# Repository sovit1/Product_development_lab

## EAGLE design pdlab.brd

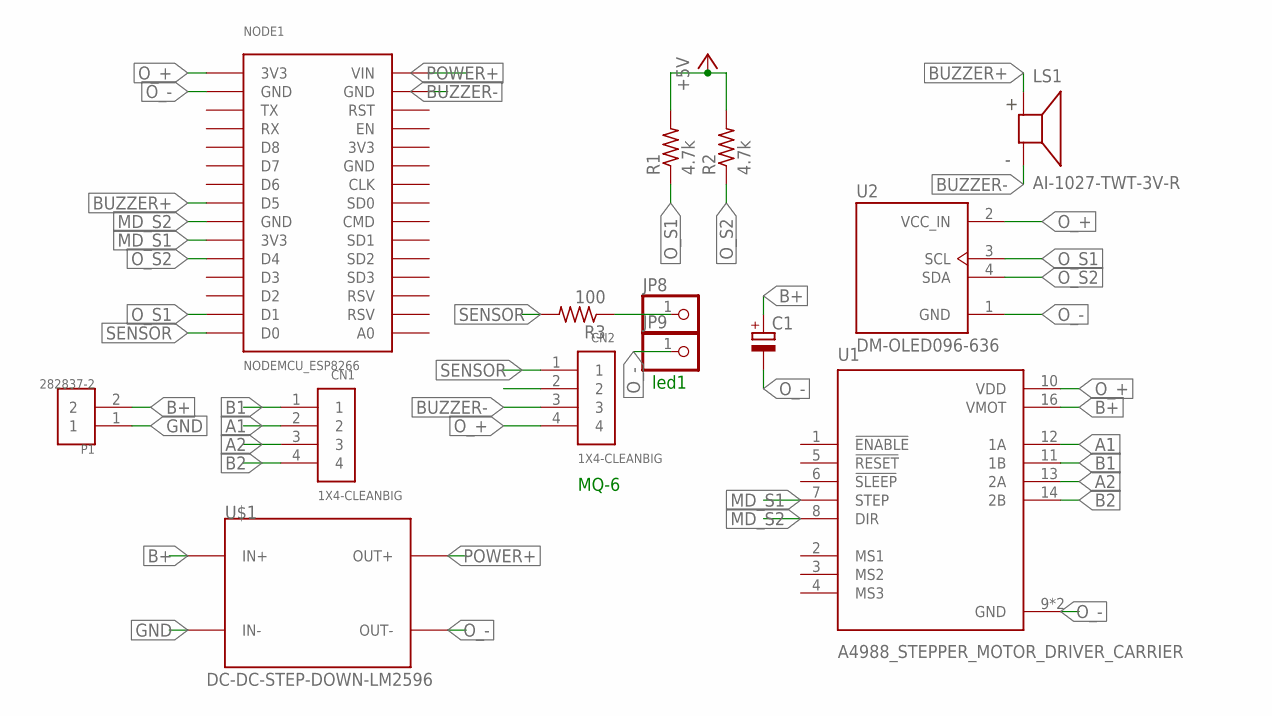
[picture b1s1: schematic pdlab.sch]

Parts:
C1: CPOL-EUE2,5-6E; E2,5-6E
CN1, CN2: 1X4-CLEANBIG; 1X04-CLEANBIG
JP8, JP9: PINHD-1X1CB; 1X01-CLEANBIG
LS1: AI-1027-TWT-3V-R; XDCR_AI-1027-TWT-3V-R
NODE1: NODEMCU_ESP8266
P1: 282837-2; TE_282837-2
R1, R2: 4.7k; 0204/7
R3: 100; 0204/7
U1: A4988_STEPPER_MOTOR_DRIVER_CARRIER; MODULE_A4988_STEPPER_MOTOR_DRIVER_CARRIER
U2: DM-OLED096-636; MODULE_DM-OLED096-636
U$1: DC-DC-STEP-DOWN-LM2596

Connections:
3V3: NODE1.3V3@3 (3V3)
+5V: R1.2, R2.2
A1: CN1.2, U1.12 (1A)
A2: CN1.3, U1.13 (2A)
B1: CN1.1, U1.11 (1B)
B2: CN1.4, U1.14 (2B)
B+: C1.+, P1.2, U1.16 (VMOT), U$1.IN+
BUZZER+: LS1.P, NODE1.D5
BUZZER-: CN2.3, LS1.N, NODE1.GND@4 (GND)
GND: NODE1.GND@3 (GND), P1.1, U$1.IN-
MD_S1: NODE1.3V3@2 (3V3), U1.7 (STEP)
MD_S2: NODE1.GND@2 (GND), U1.8 (DIR)
unnamed: JP8.1, R3.1
O_+: CN2.4, NODE1.3V3@1 (3V3), U1.10 (VDD), U2.2 (VCC_IN)
O_-: C1.-, JP9.1, NODE1.GND@1 (GND), U1.9 (GND), U1.15 (GND), U2.1 (GND), U$1.OUT-
O_S1: NODE1.D1, R1.1, U2.3 (SCL)
O_S2: NODE1.D4, R2.1, U2.4 (SDA)
POWER+: NODE1.VIN, U$1.OUT+
SENSOR: CN2.1, NODE1.D0, R3.2

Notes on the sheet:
led1
MQ-6

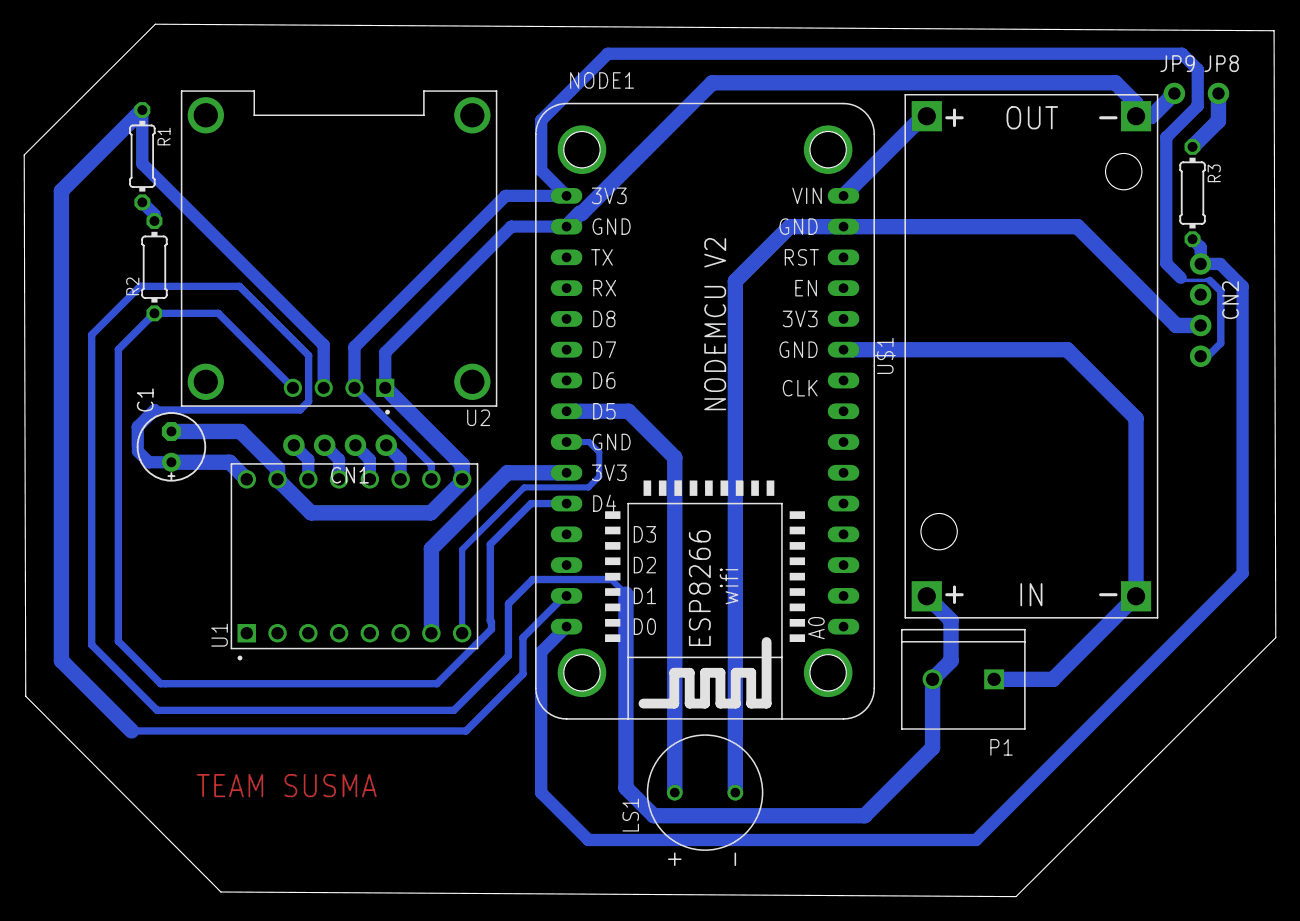
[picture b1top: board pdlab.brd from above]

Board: 2 copper layers, 103.3 x 72.0 mm, 14 parts (0 on the bottom side), 18 nets.

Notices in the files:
parts and their libraries:
diy-modules: Released under the Creative Commons Attribution 4.0 International License: http://creativecommons.org/licenses/by/4.0
